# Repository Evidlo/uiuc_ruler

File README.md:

# uiuc_ruler

PCB ruler for UIUC

## Ordering Notes

- JLCPCB.com
- Matte black solder mask
- Immersion gold (ENIG)
- 1.6mm thickness

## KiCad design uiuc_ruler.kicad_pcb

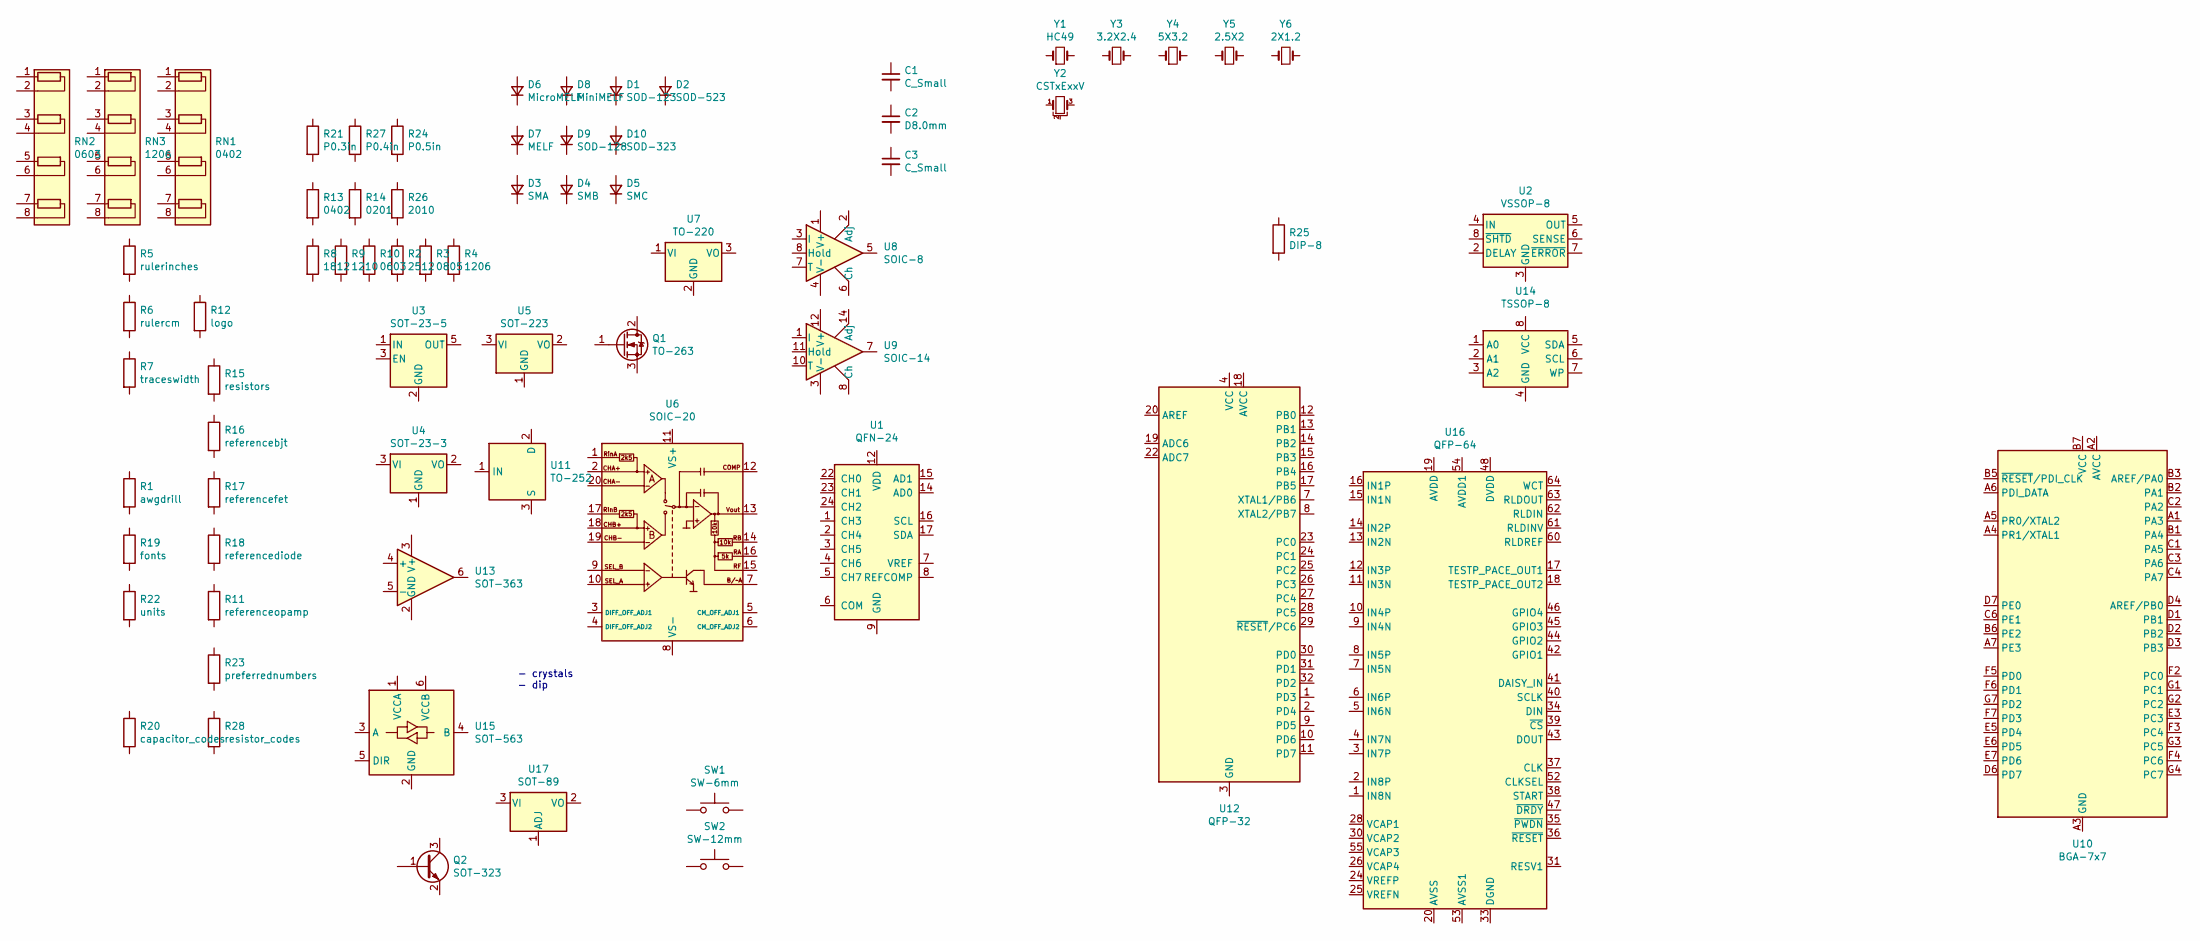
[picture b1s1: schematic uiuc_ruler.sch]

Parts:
C1: C_Small; cap_d5_p2.5
C2: D8.0mm; cap_d7.5_p3.5
C3: C_Small; cap_d10_p5
D1: SOD-123; D_SOD-123
D2: SOD-523; D_SOD-523
D3: SMA; D_SMA
D4: SMB; D_SMB
D5: SMC; D_SMC
D6: MicroMELF; D_MicroMELF
D7: MELF; D_MELF
D8: MiniMELF; D_MiniMELF
D9: SOD-128; D_SOD-128
D10: SOD-323; D_SOD-323
Q1: TO-263; TO-263-2
Q2: SOT-323; SOT-323_SC-70
R1: awgdrill
R2: 2512; R_2512_6332Metric
R3: 0805; R_0805_2012Metric
R4: 1206; R_1206_3216Metric
R5: rulerinches
R6: rulercm
R7: traceswidth; traceswidths
R8: 1812; R_1812_4532Metric
R9: 1210; R_1210_3225Metric
R10: 0603; R_0603_1608Metric
R11: referenceopamp
R12: logo
R13: 0402; R_0402_1005Metric
R14: 0201; R_0201_0603Metric
R15: resistors; resistor
R16: referencebjt
R17: referencefet
R18: referencediode
R19: fonts; fontsize
R20: capacitor_codes
R21: P0.3in; R_Axial_DIN0204_L3.6mm_D1.6mm_P7.62mm_Horizontal
R22: units
R23: preferrednumbers
R24: P0.5in; R_Axial_DIN0309_L9.0mm_D3.2mm_P12.70mm_Horizontal
R25: DIP-8; DIP-8_W8.89mm_SMDSocket_LongPads
R26: 2010; R_2010_5025Metric
R27: P0.4in; R_Axial_DIN0207_L6.3mm_D2.5mm_P10.16mm_Horizontal
R28: resistor_codes
RN1: 0402; R_Array_Convex_4x0402
RN2: 0603; R_Array_Convex_4x0603
RN3: 1206; R_Array_Convex_4x1206
SW1: SW-6mm; SW_PUSH_6mm
SW2: SW-12mm; SW_PUSH-12mm
U1: QFN-24; QFN-24-1EP_4x4mm_P0.5mm_EP2.6x2.6mm
U2: VSSOP-8; VSSOP-8_2.3x2mm_P0.5mm
U3: SOT-23-5
U4: SOT-23-3; SOT-23
U5: SOT-223; SOT-223-3_TabPin2
U6: SOIC-20; SOIC-20W_7.5x12.8mm_P1.27mm
U7: TO-220; TO-220-3_Vertical
U8: SOIC-8; SOIC-8_3.9x4.9mm_P1.27mm
U9: SOIC-14; SOIC-14_3.9x8.7mm_P1.27mm
U10: BGA-7x7; VFBGA-49_5.0x5.0mm_Layout7x7_P0.65mm
U11: TO-252; TO-252-3_TabPin2
U12: QFP-32; TQFP-32_7x7mm_P0.8mm
U13: SOT-363; SOT-363_SC-70-6
U14: TSSOP-8; TSSOP-8_4.4x3mm_P0.65mm
U15: SOT-563
U16: QFP-64; TQFP-64_10x10mm_P0.5mm
U17: SOT-89; SOT-89-3
Y1: HC49; Crystal_SMD_HC49-SD
Y2: CSTxExxV; Resonator_SMD_muRata_CSTxExxV-3Pin_3.0x1.1mm
Y3: 3.2X2.4; Crystal_SMD_3225-4Pin_3.2x2.5mm
Y4: 5X3.2; Crystal_SMD_Qantek_QC5CB-2Pin_5x3.2mm
Y5: 2.5X2; Crystal_SMD_EuroQuartz_X22-4Pin_2.5x2.0mm
Y6: 2X1.2; Crystal_SMD_3215-2Pin_3.2x1.5mm

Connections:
unnamed: U1.9 (GND), U1.10 (GND), U1.11 (GND), U1.18 (GND), U1.19 (GND), U1.20 (GND), U1.25 (GND)
unnamed: U1.12 (VDD), U1.13 (VDD), U1.21 (VDD)
unnamed: U10.A3 (GND), U10.B4 (GND), U10.C5 (GND), U10.C7 (GND), U10.D5 (GND), U10.E1 (GND), U10.E2 (GND), U10.E4 (GND), U10.G5 (GND)
unnamed: U10.B7 (VCC), U10.F1 (VCC), U10.G6 (VCC)
unnamed: U12.4 (VCC), U12.6 (VCC)
unnamed: U12.3 (GND), U12.5 (GND), U12.21 (GND)
unnamed: U13.1 (GND), U13.2 (GND)
unnamed: U16.19 (AVDD), U16.21 (AVDD), U16.22 (AVDD), U16.56 (AVDD), U16.59 (AVDD)
unnamed: U16.20 (AVSS), U16.23 (AVSS), U16.32 (AVSS), U16.57 (AVSS), U16.58 (AVSS)
unnamed: U16.33 (DGND), U16.49 (DGND), U16.51 (DGND)
unnamed: U16.48 (DVDD), U16.50 (DVDD)

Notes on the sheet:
- crystals - dip

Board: 2 copper layers, 69 parts (1 on the bottom side), 11 nets, no tracks yet.

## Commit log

2021-06-07 init commit
2021-08-16 add footprints
2021-08-31 add render, correct opamp polarity
2022-03-08 add revisions
2022-03-08 remove logo
2022-03-08 add picture
2022-05-11 add gitignore, logo, cache file
2025-02-05 add order notes, update resistor/capacitor diagram, add diode label
